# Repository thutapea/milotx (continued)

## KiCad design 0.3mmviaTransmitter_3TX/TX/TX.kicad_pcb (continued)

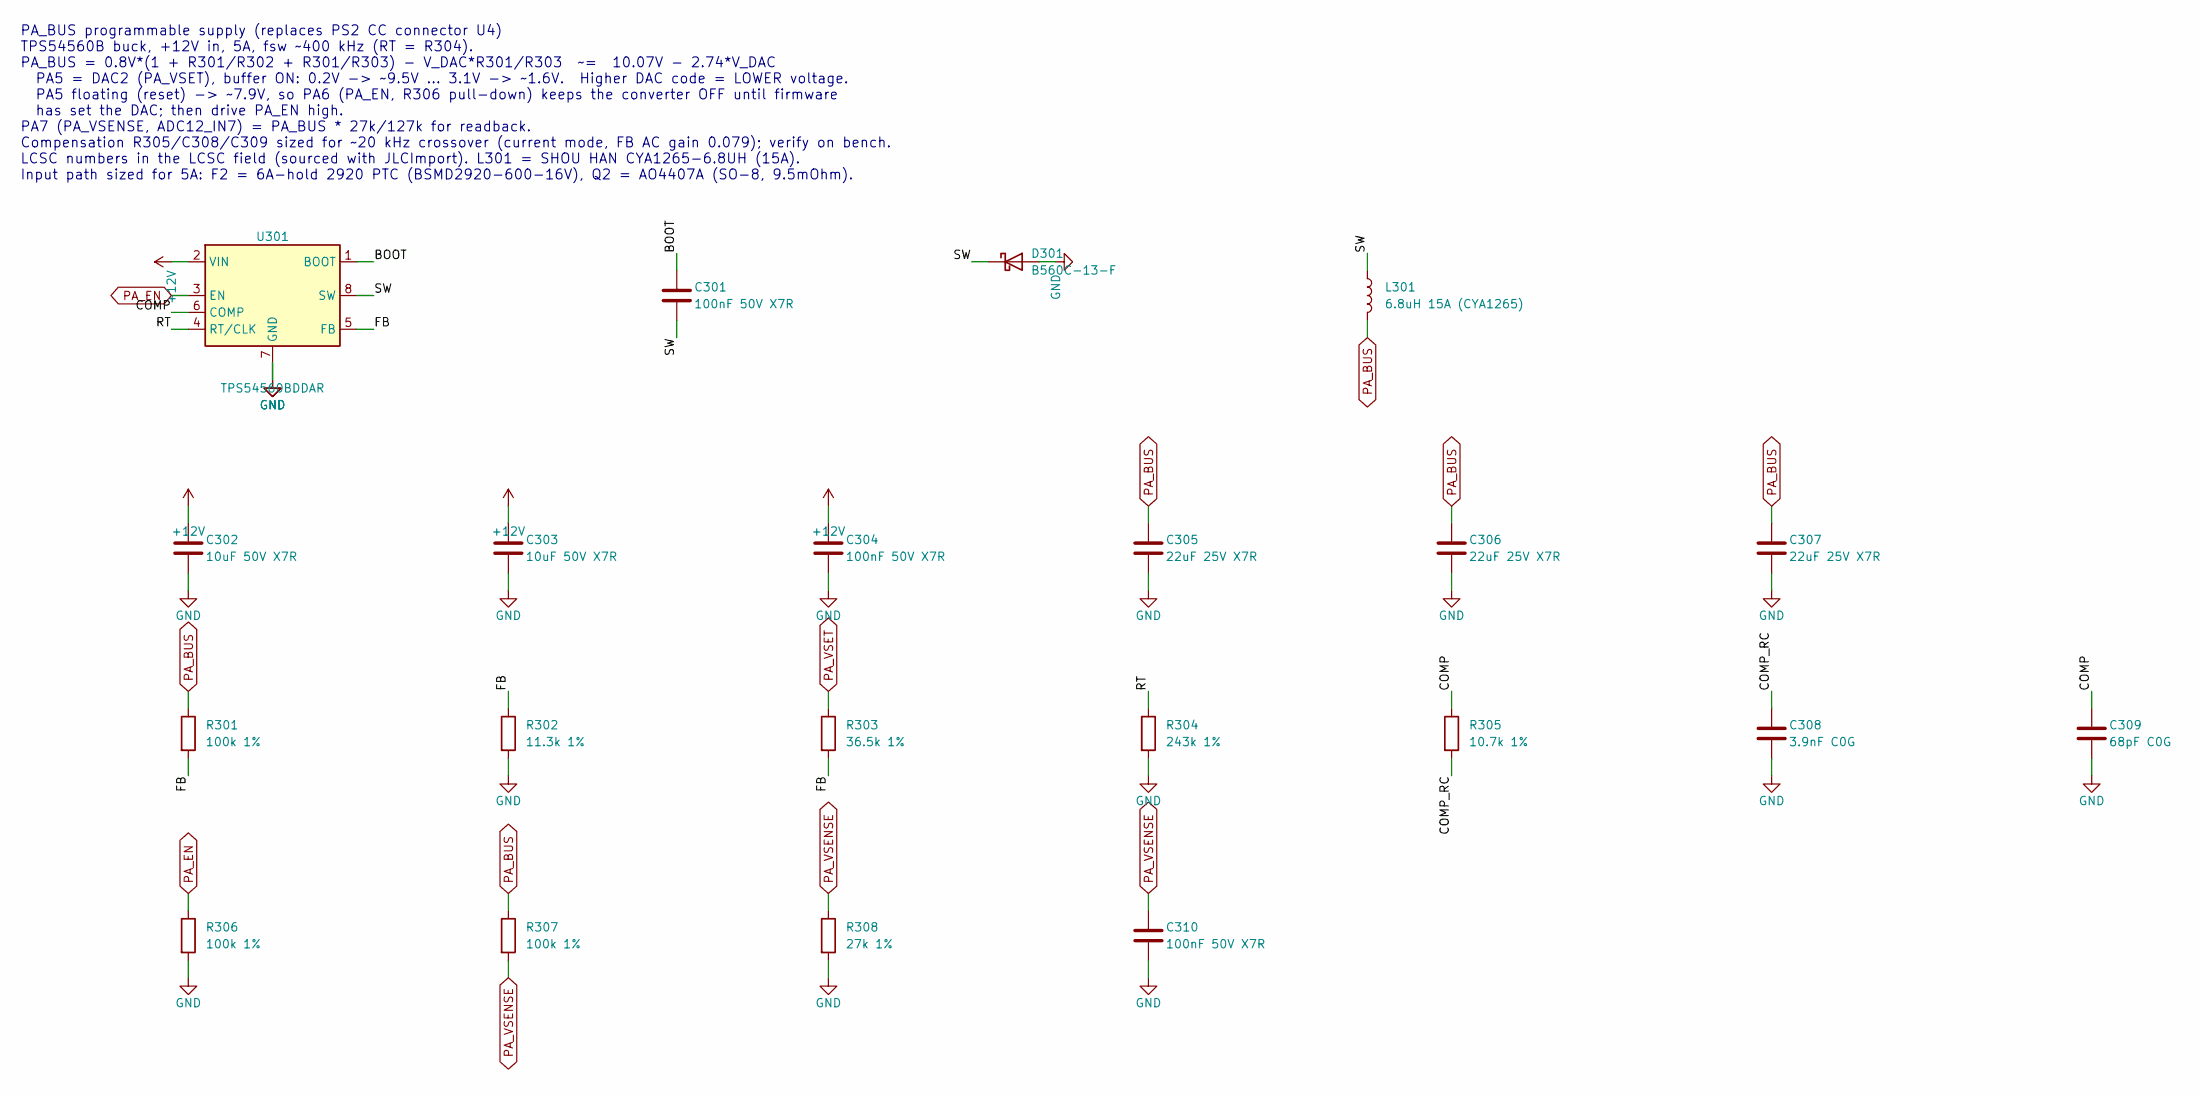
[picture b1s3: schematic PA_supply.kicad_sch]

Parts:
C301, C304, C310: 100nF 50V X7R; C_0603_1608Metric; Manufacturer Part CC0603KRX7R9BB104; LCSC C14663
C302, C303: 10uF 50V X7R; C_1210_3225Metric; Manufacturer Part CS3225X7R106K500NRL; LCSC C2918502
C305, C306, C307: 22uF 25V X7R; C_1210_3225Metric; Manufacturer Part CS3225X7R226K250NRL; LCSC C2918511
C308: 3.9nF C0G; C_0603_1608Metric; Manufacturer Part GRM1885C1H392JA01D; LCSC C415537
C309: 68pF C0G; C_0603_1608Metric; Manufacturer Part CL10C680JB8NNNC; LCSC C28262
D301: B560C-13-F; D_SMC; Manufacturer Part B560C-13-F; LCSC C85100
L301: 6.8uH 15A (CYA1265); CYA1265-6_8UH; Manufacturer Part CYA1265-6.8UH; LCSC C19268667
R301, R306, R307: 100k 1%; R_0603_1608Metric; Manufacturer Part 0603WAF1003T5E; LCSC C25803
R302: 11.3k 1%; R_0603_1608Metric; Manufacturer Part 0603WAF1132T5E; LCSC C22860
R303: 36.5k 1%; R_0603_1608Metric; Manufacturer Part 0603WAF3652T5E; LCSC C23029
R304: 243k 1%; R_0603_1608Metric; Manufacturer Part 0603WAF2433T5E; LCSC C23351
R305: 10.7k 1%; R_0603_1608Metric; Manufacturer Part 0603WAF1072T5E; LCSC C22857
R308: 27k 1%; R_0603_1608Metric; Manufacturer Part 0603WAF2702T5E; LCSC C22967
U301: TPS54560BDDAR; Texas_R-PDSO-G8_EP2.95x4.9mm_Mask2.4x3.1mm; Manufacturer Part TPS54560BDDAR; LCSC C1850354

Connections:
+12V: C302.1, C303.1, C304.1, U301.2 (VIN); also elsewhere on the board
/PA_BUS supply/BOOT: C301.1, U301.1 (BOOT)
/PA_BUS supply/COMP: C309.1, R305.1, U301.6 (COMP)
/PA_BUS supply/COMP_RC: C308.1, R305.2
/PA_BUS supply/FB: R301.2, R302.1, R303.2, U301.5 (FB)
/PA_BUS supply/RT: R304.1, U301.4 (RT/CLK)
/PA_BUS supply/SW: C301.2, D301.1 (K), L301.1, U301.8 (SW)
GND: C302.2, C303.2, C304.2, C305.2, C306.2, C307.2, C308.2, C309.2, C310.2, D301.2 (A), R302.2, R304.2, R306.2, R308.2, U301.7 (GND), U301.9 (GND); also elsewhere on the board
PA_BUS: C305.1, C306.1, C307.1, L301.2, R301.1, R307.1; also elsewhere on the board
PA_EN: R306.1, U301.3 (EN); also elsewhere on the board
PA_VSENSE: C310.1, R307.2, R308.1; also elsewhere on the board
PA_VSET: R303.1; also elsewhere on the board

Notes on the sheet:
PA_BUS programmable supply (replaces PS2 CC connector U4) TPS54560B buck, +12V in, 5A, fsw ~400 kHz (RT = R304). PA_BUS = 0.8V*(1 + R301/R302 + R301/R303) - V_DAC*R301/R303 ~= 10.07V - 2.74*V_DAC PA5 = DAC2 (PA_VSET), buffer ON: 0.2V -> ~9.5V ... 3.1V -> ~1.6V. Higher DAC code = LOWER voltage. PA5 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

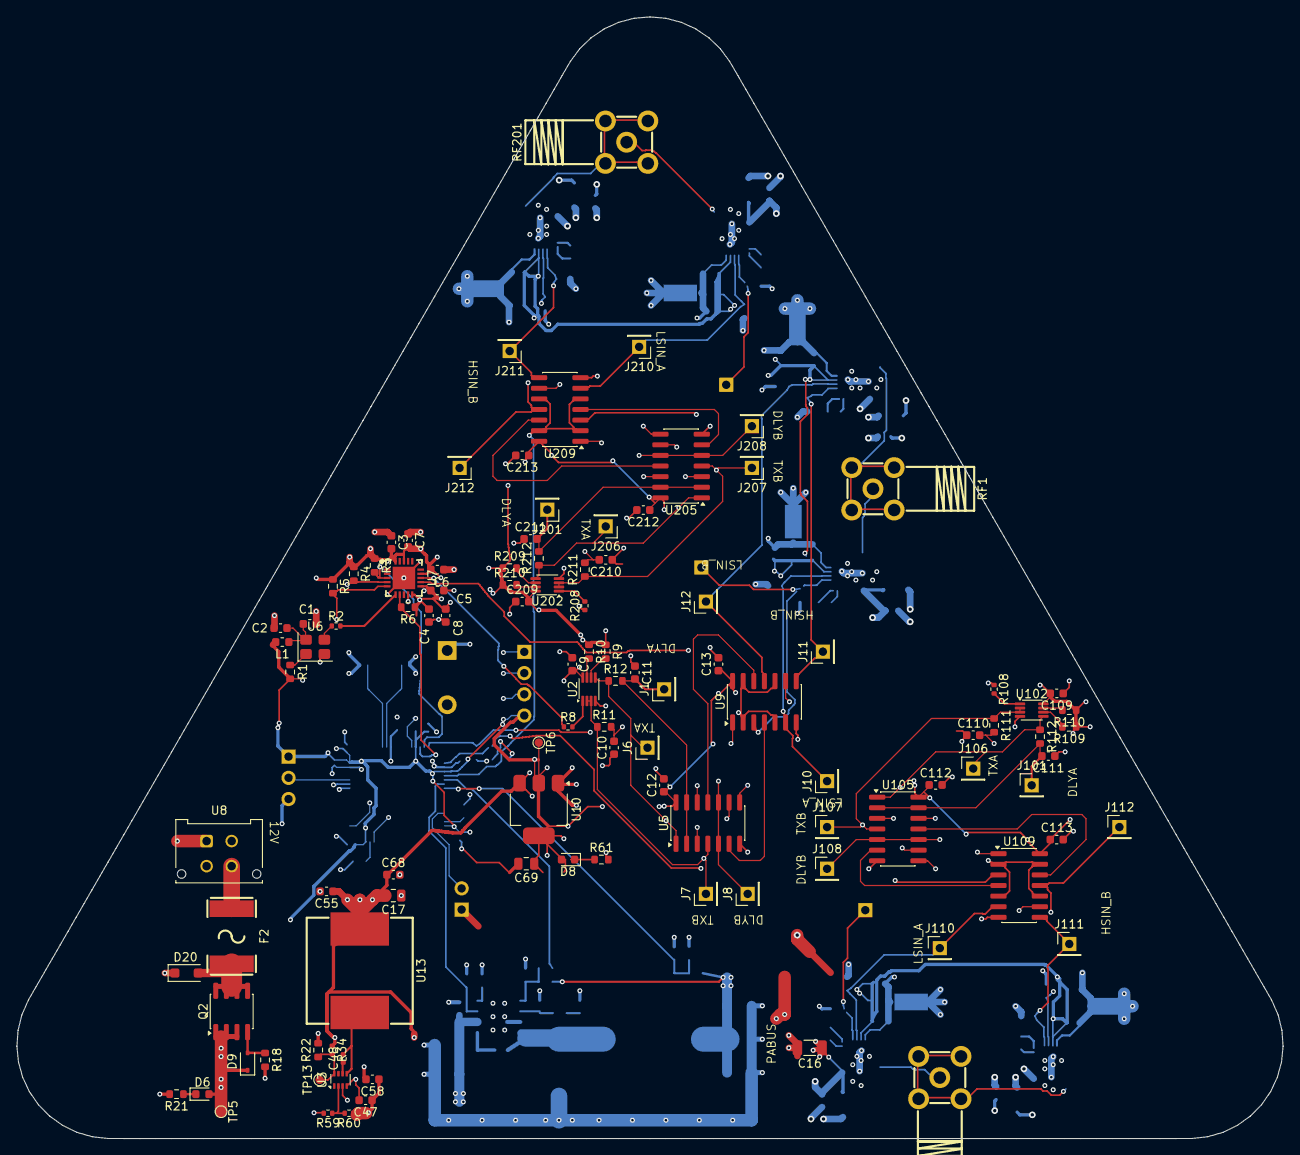
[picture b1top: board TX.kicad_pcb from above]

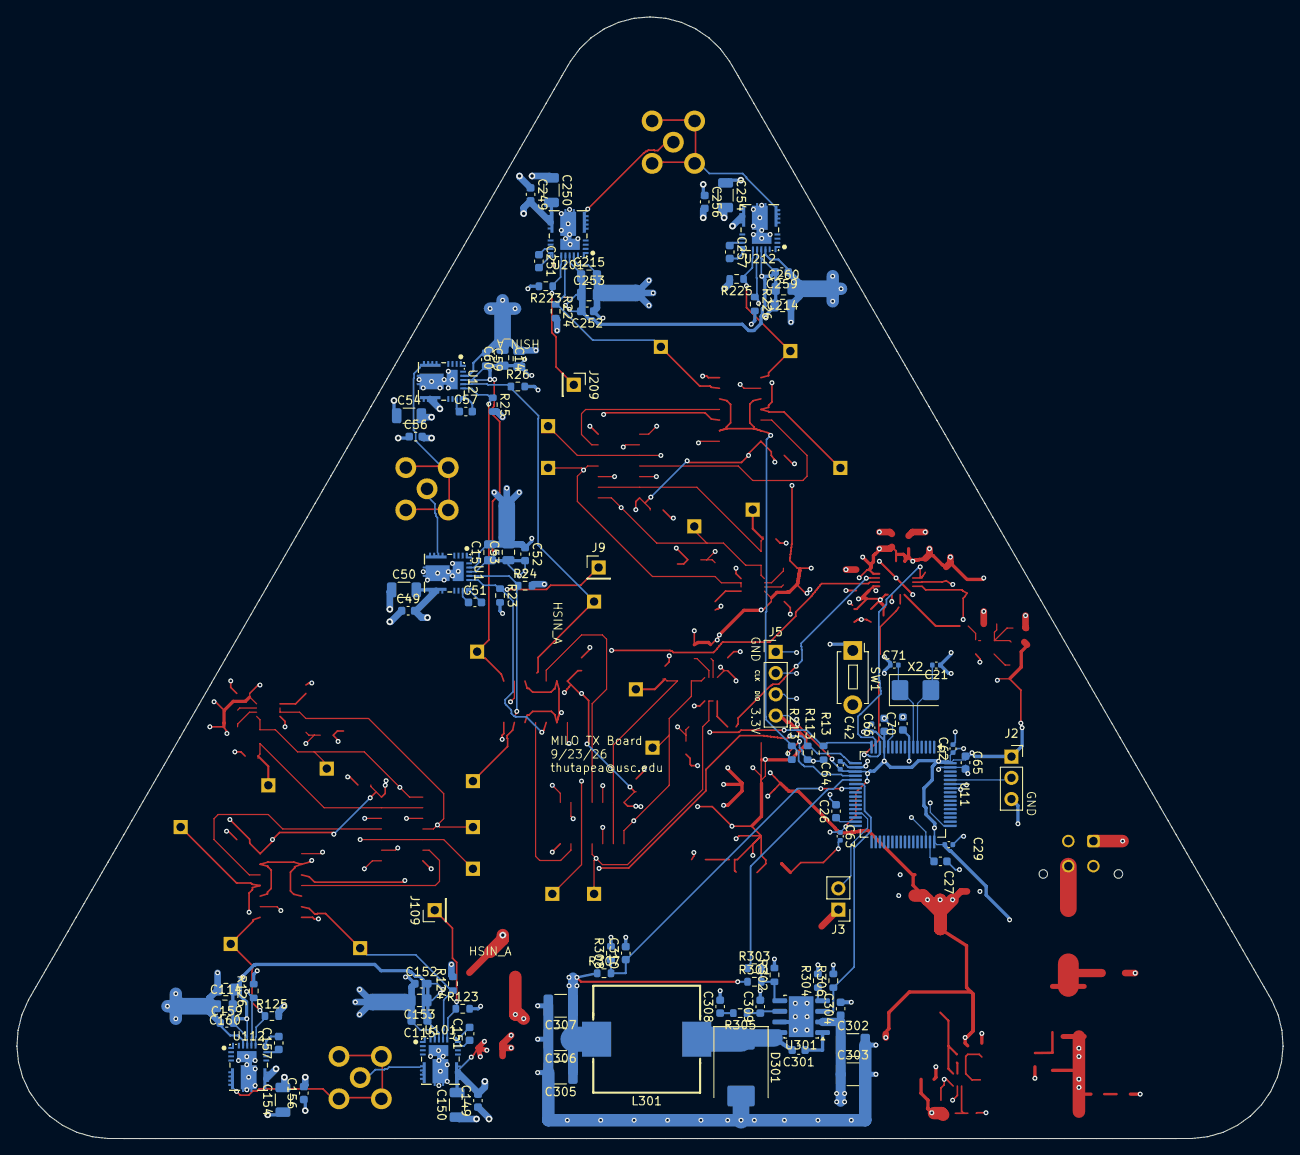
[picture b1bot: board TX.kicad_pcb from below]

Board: 6 copper layers, 151.6 x 134.3 mm, 213 parts (105 on the bottom side), 115 nets.

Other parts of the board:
TP5, TP6, TP13: TestPoint_Small; TestPoint_Pad_D1.0mm

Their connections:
+3.3V: TP6.1 (1_1); also elsewhere on the board
+12V: TP5.1 (1_1); also elsewhere on the board
unnamed 90: TP13.1 (1_1); also elsewhere on the board

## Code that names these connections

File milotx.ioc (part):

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Mcu.Name=STM32F405RGTx
Mcu.Package=LQFP64
Mcu.UserName=STM32F405RGTx
PA0-WKUP.Signal=GPIO_Output
PA13.Mode=Serial_Wire
PA13.Signal=SYS_JTMS-SWDIO
PA14.Mode=Serial_Wire
PA14.Signal=SYS_JTCK-SWCLK
PB10.Mode=Half_duplex(single_wire_mode)
PB10.Signal=USART3_TX
PB6.Mode=I2C
PB6.Signal=I2C1_SCL
PB7.Mode=I2C
PB7.Signal=I2C1_SDA
PH0-OSC_IN.Mode=HSE-External-Oscillator
PH0-OSC_IN.Signal=RCC_OSC_IN
PH1-OSC_OUT.Mode=HSE-External-Oscillator
PH1-OSC_OUT.Signal=RCC_OSC_OUT
RCC.HSE_VALUE=8000000
RCC.SYSCLKFreq_VALUE=168000000
RCC.SYSCLKSource=RCC_SYSCLKSOURCE_PLLCLK
board=custom
